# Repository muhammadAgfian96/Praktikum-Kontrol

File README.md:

# Praktikum-Kontrol
code praktikum kontrol di TF Fisika Telkom University

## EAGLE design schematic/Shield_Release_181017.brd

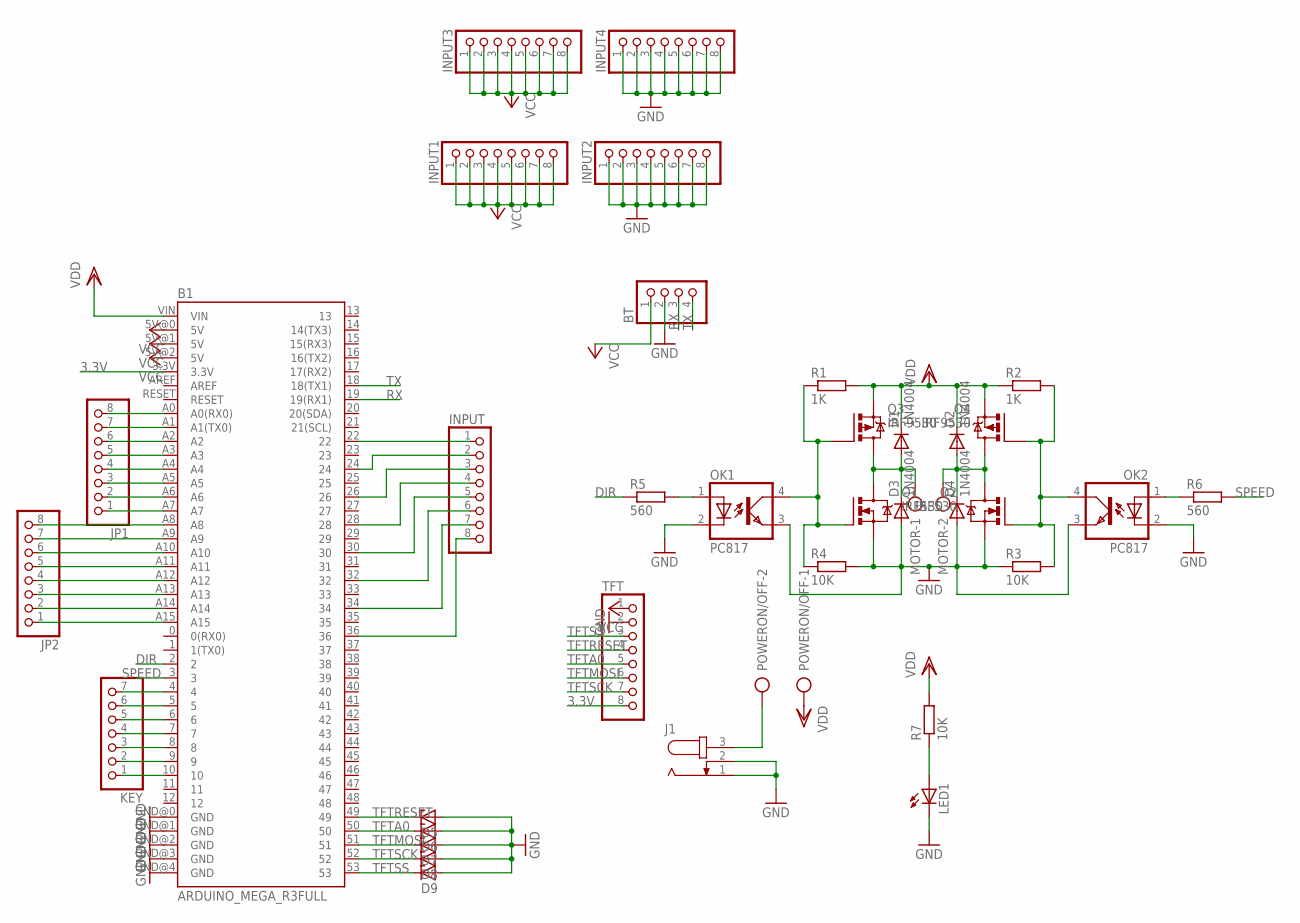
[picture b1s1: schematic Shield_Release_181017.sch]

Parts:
B1: ARDUINO_MEGA_R3FULL; ARDUINO_MEGA
BT: PINHD-1X4; 1X04
D1, D2, D3, D4: 1N4004; DO41-10
D5, D6, D7, D8, D9: ZENER-DIODEDO41Z10; DO41Z10
INPUT, INPUT1, INPUT2, INPUT3, INPUT4: PINHD-1X8; 1X08
J1: JACK-PLUG0; SPC4077
JP1, JP2: PINHD-1X8; 1X08
KEY: PINHD-1X7; 1X07
LED1: LED5MM
MOTOR: AK300/2
OK1, OK2: PC817; DIL04
POWERON/OFF: AK300/2
Q1, Q2: IRF530; TO220BV
Q3, Q4: IRF9530; TO220BV
R1, R2: 1K; 0204/7
R3, R4, R7: 10K; 0204/7
R5, R6: 560; 0204/7
TFT: PINHD-1X8; 1X08

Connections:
3.3V: B1.3.3V, TFT.8
DIR: B1.2, R5.1
GND: B1.GND@0 (GND), B1.GND@1 (GND), B1.GND@2 (GND), B1.GND@3 (GND), B1.GND@4 (GND), BT.2, D3.A, D4.A, D5.A, D6.A, D7.A, D8.A, D9.A, INPUT2.1, INPUT2.2, INPUT2.3, INPUT2.4, INPUT2.5, INPUT2.6, INPUT2.7, INPUT2.8, INPUT4.1, INPUT4.2, INPUT4.3, INPUT4.4, INPUT4.5, INPUT4.6, INPUT4.7, INPUT4.8, J1.1, J1.2, LED1.K (C), OK1.2 (C), OK1.3 (EMIT), OK2.2 (C), OK2.3 (EMIT), Q1.S, Q2.S, R3.1, R4.2, TFT.2
unnamed: OK1.4 (COL), Q1.G, Q3.G, R1.1, R4.1
unnamed: OK1.1 (A), R5.2
unnamed: OK2.1 (A), R6.1
unnamed: OK2.4 (COL), Q2.G, Q4.G, R2.2, R3.2
unnamed: B1.10, KEY.1
unnamed: B1.9, KEY.2
unnamed: D1.A, D3.C, MOTOR.1, Q1.D, Q3.D
unnamed: D2.A, D4.C, MOTOR.2, Q2.D, Q4.D
unnamed: B1.8, KEY.3
unnamed: B1.7, KEY.4
unnamed: B1.6, KEY.5
unnamed: B1.5, KEY.6
unnamed: B1.4, KEY.7
unnamed: B1.A7, JP1.1
unnamed: B1.A6, JP1.2
unnamed: B1.A5, JP1.3
unnamed: B1.A4, JP1.4
unnamed: B1.A3, JP1.5
unnamed: B1.A2, JP1.6
unnamed: B1.A1 (A1(TX0)), JP1.7
unnamed: B1.A0 (A0(RX0)), JP1.8
unnamed: B1.A15, JP2.1
unnamed: B1.A14, JP2.2
unnamed: B1.A13, JP2.3
unnamed: B1.A12, JP2.4
unnamed: B1.A11, JP2.5
unnamed: B1.A10, JP2.6
unnamed: B1.A9, JP2.7
unnamed: B1.A8, JP2.8
unnamed: B1.22, INPUT.1
unnamed: B1.24, INPUT.2
unnamed: B1.26, INPUT.3
unnamed: B1.28, INPUT.4
unnamed: B1.30, INPUT.5
unnamed: B1.32, INPUT.6
unnamed: B1.34, INPUT.7
unnamed: B1.36, INPUT.8
unnamed: J1.3, POWERON/OFF.2
unnamed: LED1.A, R7.1
RX: B1.19 (19(RX1)), BT.3
SPEED: B1.3, R6.2
TFTA0: B1.50, D6.C, TFT.5
TFTMOSI: B1.51, D7.C, TFT.6
TFTRESET: B1.49, D5.C, TFT.4
TFTSCK: B1.52, D8.C, TFT.7
TFTSS: B1.53, D9.C, TFT.3
TX: B1.18 (18(TX1)), BT.4
VCC: B1.5V@0 (5V), B1.5V@1 (5V), B1.5V@2 (5V), BT.1, INPUT1.1, INPUT1.2, INPUT1.3, INPUT1.4, INPUT1.5, INPUT1.6, INPUT1.7, INPUT1.8, INPUT3.1, INPUT3.2, INPUT3.3, INPUT3.4, INPUT3.5, INPUT3.6, INPUT3.7, INPUT3.8, TFT.1
VDD: B1.VIN, D1.C, D2.C, POWERON/OFF.1, Q3.S, Q4.S, R1.2, R2.1, R7.2

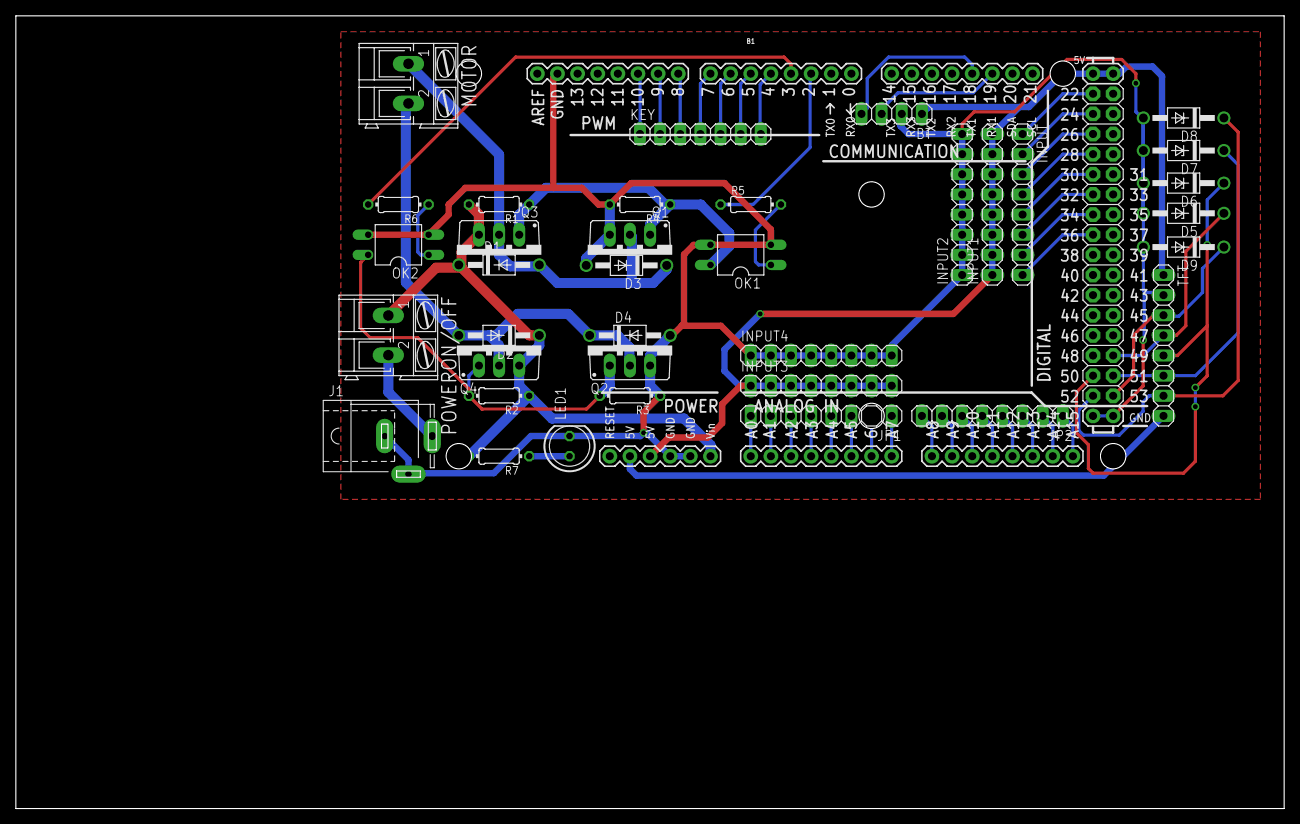
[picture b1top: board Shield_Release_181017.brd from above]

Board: 2 copper layers, 160.0 x 100.0 mm, 37 parts (0 on the bottom side), 52 nets.

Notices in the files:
parts and their libraries:
SparkFun-Boards: Licensing: Creative Commons ShareAlike 4.0 International - https://creativecommons.org/licenses/by-sa/4.0
